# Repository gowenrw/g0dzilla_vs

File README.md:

# godzilla_vs

Godzilla VS Badge Artifacts

This is a DEFCON Indie badge created for DC32.

This is where all the files for the Badge will be stored.

This includes code and art and cad and fab files.  All the things.

## File Structure

This is the file structure of this repository

* [/](/README.md) - YOU ARE HERE
* [/art/](./art/) - Artwork and other graphics created by this project
  * [/art/inspiration/](./art/inspiration/) - Art and graphics pulled f6 other sources used as inspiration for this project
  * [/art/fonts/](./art/fonts/) - Fonts used in art and graphics
* [/code/](./code/) - All project related Code / Firmware
* [/docs/](./docs/) - Documentation created by this project including web pages
* [/eda/](./eda/) - Electronic Design Automation files (i.e. KiCad)
  * [/eda/godzilla_vs/](./eda/godzilla_vs/) - KiCad 7.x project folder for the godzilla_vs PCB
* [/reference_parts/](./reference_parts/) - Documentation pulled from other sources related to components
* [/README.md](/README.md) - This File
* [/LICENSE](/LICENSE) - Currently set to MIT

Note: the reference_parts directory is a link to a submodule repository.
To add it use the following cmd after cloning this:
```
git submodule update --init --recursive
```
If adding for the first time (i.e., it is not linked in the remote master) use this:
```
git submodule add https://github.com/gowenrw/reference_parts reference_parts
```
This will make a link to the current commit of that repo.
To update it to a newer commit after its been added use this cmd:
```
git submodule update --remote
```

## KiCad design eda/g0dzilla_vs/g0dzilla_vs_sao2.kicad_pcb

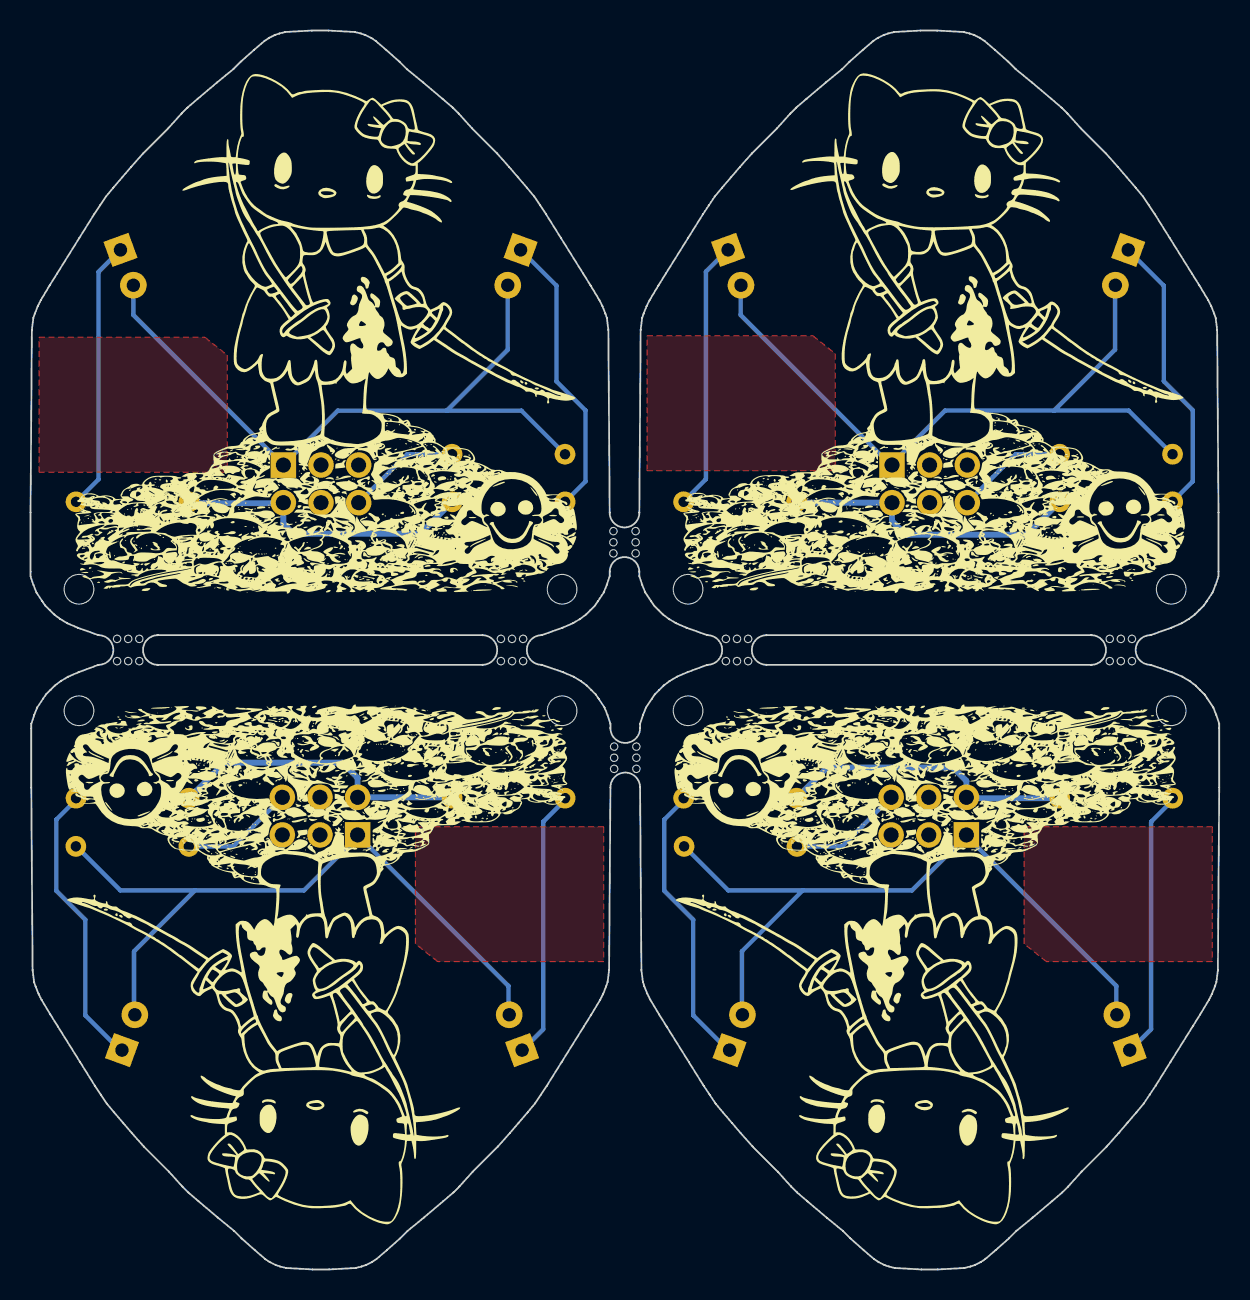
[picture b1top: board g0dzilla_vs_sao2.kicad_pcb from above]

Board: 2 copper layers, 80.2 x 83.6 mm, 36 parts (0 on the bottom side), 20 nets.

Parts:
D11, D12, D21, D22, D31, D32, D41, D42: LED_3mm; LED_D3.0mm-2-std_back
Fold: LED_Fold_Indicator_1; LED_Fold_Indicator_back
Fold#2, Fold#3, Fold#4, Fold#5, Fold#6, Fold#7, Fold#8: LED_Fold_Indicator_1; LED_Fold_Indicator_back
JSAO1, JSAO2, JSAO3, JSAO4: Conn_02x03_SAO; SAOv169-SAOv3-2x3
R11, R12, R21, R22, R31, R32, R41, R42: 47R_6.3mm; R_Axial_DIN0207_L6.3_D2.5_P7.62_Horiz_back
R13: 10K_6.3mm; R_Axial_DIN0207_L6.3_D2.5_P7.62_Horiz_back
R23: 47K_6.3mm; R_Axial_DIN0207_L6.3_D2.5_P7.62_Horiz_back
R33: 100K_6.3mm; R_Axial_DIN0207_L6.3_D2.5_P7.62_Horiz_back
R43: 220K_6.3mm; R_Axial_DIN0207_L6.3_D2.5_P7.62_Horiz_back
mask_back_sao2: Back Mask; g0dzilla_vs_sao2_mask_b
mask_front_sao2: Front Mask; g0dzilla_vs_sao2_mask_f
sao_edgecuts_01: Edge Cuts; g0dzilla_vs_SAO_edgecuts_01
silk_front_sao2: Front Silk; g0dzilla_vs_sao2_silk_f

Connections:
+3.3V: D11.2 (A), D12.2 (A), JSAO1.1, R13.2
+3.3V1: D21.2 (A), D22.2 (A), JSAO2.1, R23.2
+3.3V2: D31.2 (A), D32.2 (A), JSAO3.1, R33.2
+3.3V3: D41.2 (A), D42.2 (A), JSAO4.1, R43.2
GND: JSAO1.2, R11.2, R12.2
GND1: JSAO2.2, R21.2, R22.2
GND2: JSAO3.2, R31.2, R32.2
GND3: JSAO4.2, R41.2, R42.2
unnamed: D11.1 (K), R11.1
unnamed: D12.1 (K), R12.1
unnamed: D21.1 (K), R21.1
unnamed: D22.1 (K), R22.1
unnamed: D31.1 (K), R31.1
unnamed: D32.1 (K), R32.1
unnamed: D41.1 (K), R41.1
unnamed: D42.1 (K), R42.1
unnamed: JSAO1.6, R13.1
unnamed: JSAO2.6, R23.1
unnamed: JSAO3.6, R33.1
unnamed: JSAO4.6, R43.1

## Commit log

2024-03-11 initial badge template
2024-03-11 added to art/inspiration
2024-03-12 added submodule reference_parts
2024-03-18 added ESP32 Wemos Lolin32 Lite schem footprints 3D
2024-03-18 reference_parts submodule update
2024-03-18 doc cleanup
2024-03-25 footprint and schem updates
2024-03-25 footprint and schematic updates
2024-03-25 footprint updates
2024-03-27 schematic anf footprint work
2024-03-27 esp footprint update
2024-04-02 schematic and footprint updates
2024-05-10 project rename
2024-05-13 art and eda updates
2024-06-04 edgecuts art and eda work
2024-06-05 art work
2024-06-06 art and eda work
2024-06-07 base code copied from cowboys badge
2024-06-07 face art and foorprint
2024-06-10 art and pcb prep
2024-06-12 middle pcb work
2024-06-12 eda work
2024-06-12 proto art
2024-06-17 rear pcb with crypto added
2024-06-18 sao art and eda work
2024-06-18 pcb updates
2024-06-18 rear pcb work
2024-06-20 final edits before prototype
2024-06-20 final pcbs for prototype
2024-06-26 prototype 3d viewer snapshots
2024-06-28 test code
2024-06-29 code updates
2024-07-02 new test code
2024-07-02 code updates for touch threshold and random colors
2024-07-09 h3llo kitty sao
2024-07-10 first code rev with ctf complete
2024-07-11 started web docs
2024-07-11 doc updates
2024-07-11 make build scripts executable
2024-07-11 fix cnfig file name
    All the scripts reference "arduino-cli.yml".
2024-07-13 updated assembly doc
2024-08-26 code doc link update
